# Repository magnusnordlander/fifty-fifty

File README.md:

# fifty-fifty
A grinder controller for my Mazzer Major

## Status
This project is in use and development. Current PCB Revision is Rev C.

*There will be a Rev D PCB*. The Rev D PCB will adjust the fit for a Futurekit FB20 box (it's currently slightly too large, and the mounting holes are misaligned). 

### Changelog

* Rev A: First revision board
* Rev B: Substantial changes. ADS1232 load cell interface, SMT components, fully populated UEXT connector (was printed).
  * Errata: Resistor R2 never should have existed. Remove R2 or cut trace from R2 to GND.
  * Errata: R3 and R4 silk screens are flipped around. They're the same value though, so it doesn't make any material difference.
* Rev C: Removed the resistor that was R2 in Rev B (hasn't been printed), fixed silk screen, added dots for SMT ICs.
  * Errata: Doesn't quite fit in the intended Futurekit FB20 box.

## Overview

This is an Arduino based grinder controller for my Mazzer Major. It has a display and is controlled by a rotary encoder. It also contains a PCB schematic.

## Features

* Grinder control via a simple to use interface, controlled by a rotary encoder
* Timed grinding
* Grind by weight
  * An ADS1232 load cell interface, sampling a load cell at 80 SPS.
  * High accuracy
  * Fast taring

## Parts

* [Arduino Nano 33 IoT](https://www.electrokit.com/en/product/arduino-nano-33-iot-with-headers/)
* A Solid-state relay
  * I'm using a [Fotek SSR-40 DA clone](https://www.electrokit.com/en/product/solid-state-relay-3-32v-40a/), because that's what came with my used grinder when I bought it
  * If you want a more high-quality component, a [Crydom-Sensata 84137000](http://www.crydom.com/en/products/catalog/gnssr.pdf) would be a good choice
* A high quality 5.3-6.0V power supply. I'm using a [Mean Well RS-15-5](https://www.amazon.se/gp/product/B00MWQD43U/ref=ppx_yo_dt_b_asin_title_o01_s01?ie=UTF8&psc=1). Quality matters for minimizing ADC interference. A 5V power supply with an adjustment potentiometer should do fine, the LDO will regulate anything between 5.3 and 6.0 V to 5V for the ADC. Set your PSU to 5.5V and all will be good.
* A [KY-040 style rotary encoder](https://www.electrokit.com/en/product/rotary-encoder-module/)
* An [SSD1309, SPI connected, 3.3V, 128x64 px OLED](https://www.electrokit.com/produkt/lcd-oled-2-42-12x64px-spi-i2c/)
* A [1000 g whetstone bridge load cell](https://www.electrokit.com/produkt/lastcell-1kg/)

## THT BOM

* 1 x [DIL socket 32 pin (remove 2 pins, optional but recommended)](https://www.electrokit.com/en/product/dil-socket-32-pin/) (For the Arduino)
* 1 x [PCB pin header 5.08mm 6-pole right-angle](https://www.electrokit.com/en/product/pcb-hane-5-08mm-6-pol-vinklad/) (For power, SSR and manual grind knob connection)
* 1 x [IDC box header PCB 10-p 2.54mm](https://www.electrokit.com/en/product/idc-box-header-pcb-10-p-2-54mm/) (For display connection)
* 1 x [Screw terminal 2.54mm 4-pole](https://www.electrokit.com/produkt/skruvplint-2-54mm-4-pol/) (For load cell connection)
* 1 x [5 pin 2.54mm pin header](https://www.electrokit.com/en/product/pin-header-2-54mm-1x40p-red/) (For rotary encoder connection)
* 1 x 3 pin 2.54mm pin header (For ADC debug voltage jumper)
* 1 x [2.54mm jumper](https://www.electrokit.com/produkt/bygel-2-54mm-2p-svart/)

## Anything else?

While not technically part of the board, you'll probably want some other things to make it all work:

* 1 x [Screw terminal pluggable 5.08mm 6-pole](https://www.electrokit.com/en/product/skruvplint-pluggbar-5-08mm-6-pol/)
* 1 x 10 pin IDC flat cable
* 1 x 5 pin jumper wires
* Wiring
  * 0.75 mm² (or higher) copper wiring for the high voltage side
    * Preferably in standard colors, which would be blue/brown in Europe for neutral/load. Signal wire from SSR to the motor can be any other color except green/yellow. Orange is a good choice.
  * Wiring cable, I'd go for 0.20 mm² copper. Preferably in red and black.
* WAGO 221 splicing connectors
* A 100.0 g reference weight for scale calibration

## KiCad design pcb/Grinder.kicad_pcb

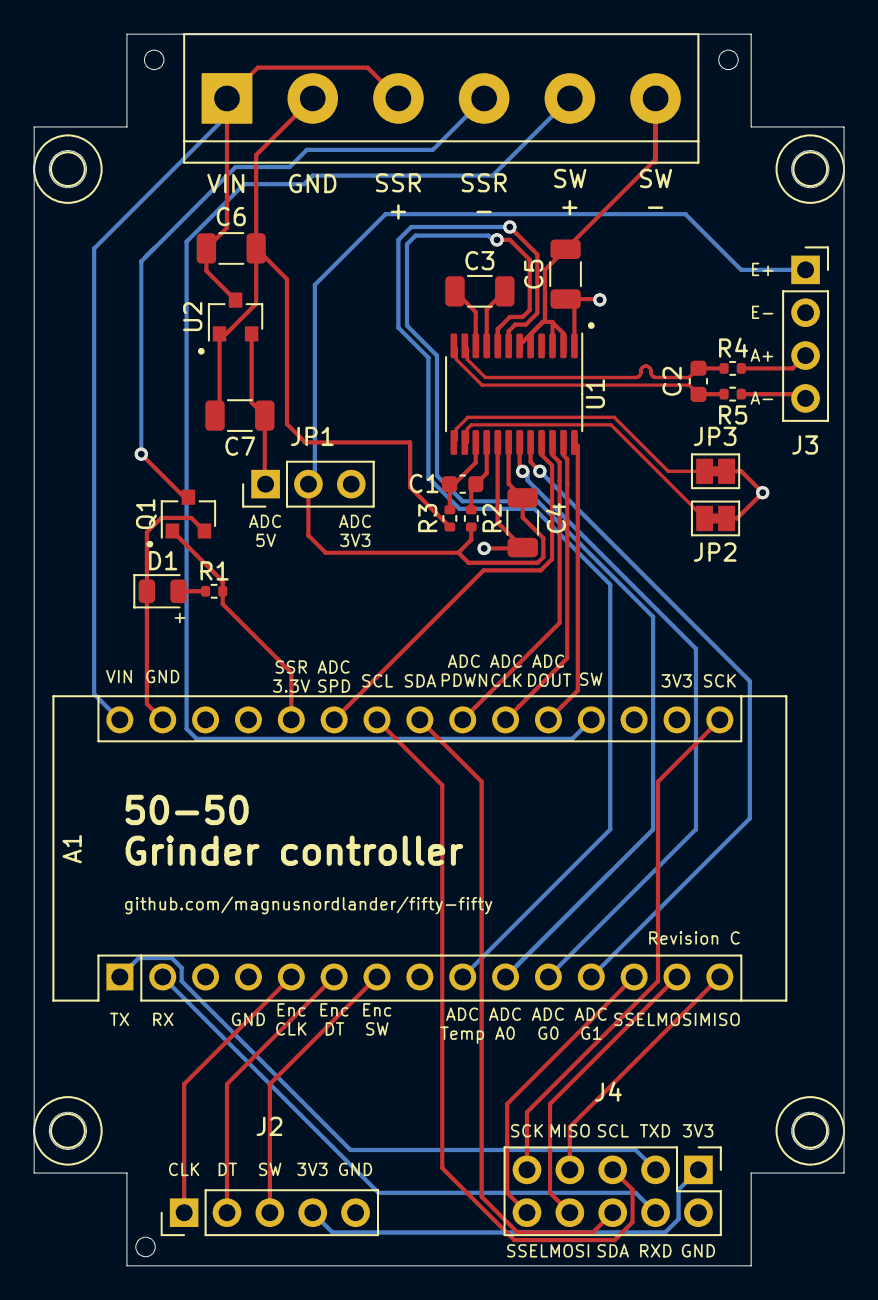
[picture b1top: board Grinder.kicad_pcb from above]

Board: 4 copper layers, 48.0 x 73.0 mm, 24 parts (0 on the bottom side), 38 nets.

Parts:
A1: Arduino Nano 33 IoT; Arduino_Nano
C1, C2: 10 nF; C_0603_1608Metric
C3, C5, C6, C7: 100 nF; C_1206_3216Metric
C4: 100nF; C_1206_3216Metric
D1: LED; LED_0805_2012Metric
J1: Conn_01x06; TerminalBlock_bornier-6_P5.08mm
J2: Conn_01x05; PinHeader_1x05_P2.54mm_Vertical
J3: Conn_01x04; PinSocket_1x04_P2.54mm_Vertical
J4: Conn_02x05_Odd_Even; PinHeader_2x05_P2.54mm_Vertical
JP1: Debug voltage; PinHeader_1x03_P2.54mm_Vertical
JP2: AINP2; SolderJumper-2_P1.3mm_Bridged_Pad1.0x1.5mm
JP3: AINN2; SolderJumper-2_P1.3mm_Bridged_Pad1.0x1.5mm
Q1: 2N7002; SOT-23
R1: R; R_0402_1005Metric
R2, R3, R4, R5: 100R; R_0402_1005Metric
U1: ADS1232IPW; TSSOP-24_4.4x7.8mm_P0.65mm
U2: XC6206P502MR; SOT-23

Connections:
3V3: A1.17, C5.1, J2.4, J4.1, JP1.3, U1.1
ADC_A0: A1.10, U1.8
ADC_CLK: A1.21, U1.23
ADC_DOUT: A1.20, U1.24
ADC_GAIN0: A1.11, U1.19
ADC_GAIN1: A1.12, U1.20
ADC_PDWN: A1.22, U1.22
ADC_SPEED: A1.25, U1.21
ADC_TEMP: A1.9, U1.7
AIN1_N: C2.2, R5.1, U1.12
AIN1_P: C2.1, R4.1, U1.11
AIN2_N: JP3.2, U1.13
AIN2_P: JP2.2, U1.14
AVDD: C4.2, J3.1, JP1.2, R2.2, U1.18
ENC_CLK: A1.5, J2.1
ENC_DT: A1.6, J2.2
ENC_SW: A1.7, J2.3
GND: A1.4, A1.29, C4.1, C5.2, C6.2, C7.2, D1.1, J1.2, J1.6, J2.5, J3.2, J4.2, JP2.1, JP3.1, Q1.2, R3.2, U1.2, U1.3, U1.5, U1.6, U1.17, U2.1
MANUAL_SW: A1.19, J1.5
unnamed: C3.1, U1.9
unnamed: C3.2, U1.10
unnamed: C7.1, JP1.1, U2.2
unnamed: D1.2, R1.1
unnamed: J3.3, R4.2
unnamed: J3.4, R5.2
REFN: C1.2, R3.1, U1.15
REFP: C1.1, R2.1, U1.16
SSR_DRAIN: J1.4, Q1.3
SSR_GATE: A1.26, Q1.1, R1.2
UEXT_MISO: A1.15, J4.7
UEXT_MOSI: A1.14, J4.8
UEXT_RX: A1.2, J4.4
UEXT_SCK: A1.16, J4.9
UEXT_SCL: A1.24, J4.5
UEXT_SDA: A1.23, J4.6
UEXT_SSEL: A1.13, J4.10
UEXT_TX: A1.1, J4.3
VIN: A1.30, C6.1, J1.1, J1.3, U2.3

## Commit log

2021-01-09 Initial import
2021-01-31 Added a menu system
2021-02-07 Ported the entire project to C++
2021-02-07 Added scrolling to menus
2021-02-08 Added grind by weight using an HX711 load cell amplifier
2021-02-09 Added weight prediction
2021-02-09 Added missing redraw
2021-02-09 Changed reaction time
2021-02-09 Adjusted reaction time again
2021-02-13 Switched to an interrupt based scale system and added a calibration routine
2021-02-13 Refactored button handling
2021-02-13 Added a reaction time setting
2021-02-14 Refactoring and visual fluff
2021-02-14 Started work on temporary targets for grinding
2021-02-14 Added temporary targets for all grinding modes
2021-02-19 Changed to an SSD1309 display
2021-02-20 Made scroll direction reversible
2021-02-20 Tweaked menu navigation
2021-02-20 Undid reverse scrolling
2021-02-21 Fixed bugs with scale and print rate of change
2021-02-21 Better scale handling
2021-02-21 Tweaks
2021-02-21 Fixed timer wraparound issues
2021-02-21 Calculate grind rate using an average of 3 points for start and end
2021-02-22 Removed debug rig define
2021-02-23 Tweaked rotation handling
2021-02-24 WIP for new PCB
2021-02-27 Handle rotation after button handling, and only if we’re not interacting with the button
2021-02-27 Added ADS1232 support
2021-02-27 More stable scale display output
2021-02-27 Fixed warning
2021-02-27 Changed pins
2021-03-04 Changed IRLZ44N for 2N7002
2021-03-05 Added stuff
2021-03-06 Final changes before ordering PCB
2021-03-06 Updated pin assignments for the ordered rev-b board
2021-03-06 Updated gitignore
2021-03-06 Fixed stuff
2021-03-06 More tweaks
2021-03-26 Updated to revision C PCB
2021-03-29 Scale refactor (#1)
    * Updated gitignore
    * WIP
    * Fixed stuff
    * Tweaks
    * Tweaks
    * More tweaks
2021-03-29 Started on some IoT stuff
    More IoT stuff
    WIP
    WIP
2021-05-10 Added photos
2022-04-02 Updated default settings and pop grind view automatically when the portafilter is removed
